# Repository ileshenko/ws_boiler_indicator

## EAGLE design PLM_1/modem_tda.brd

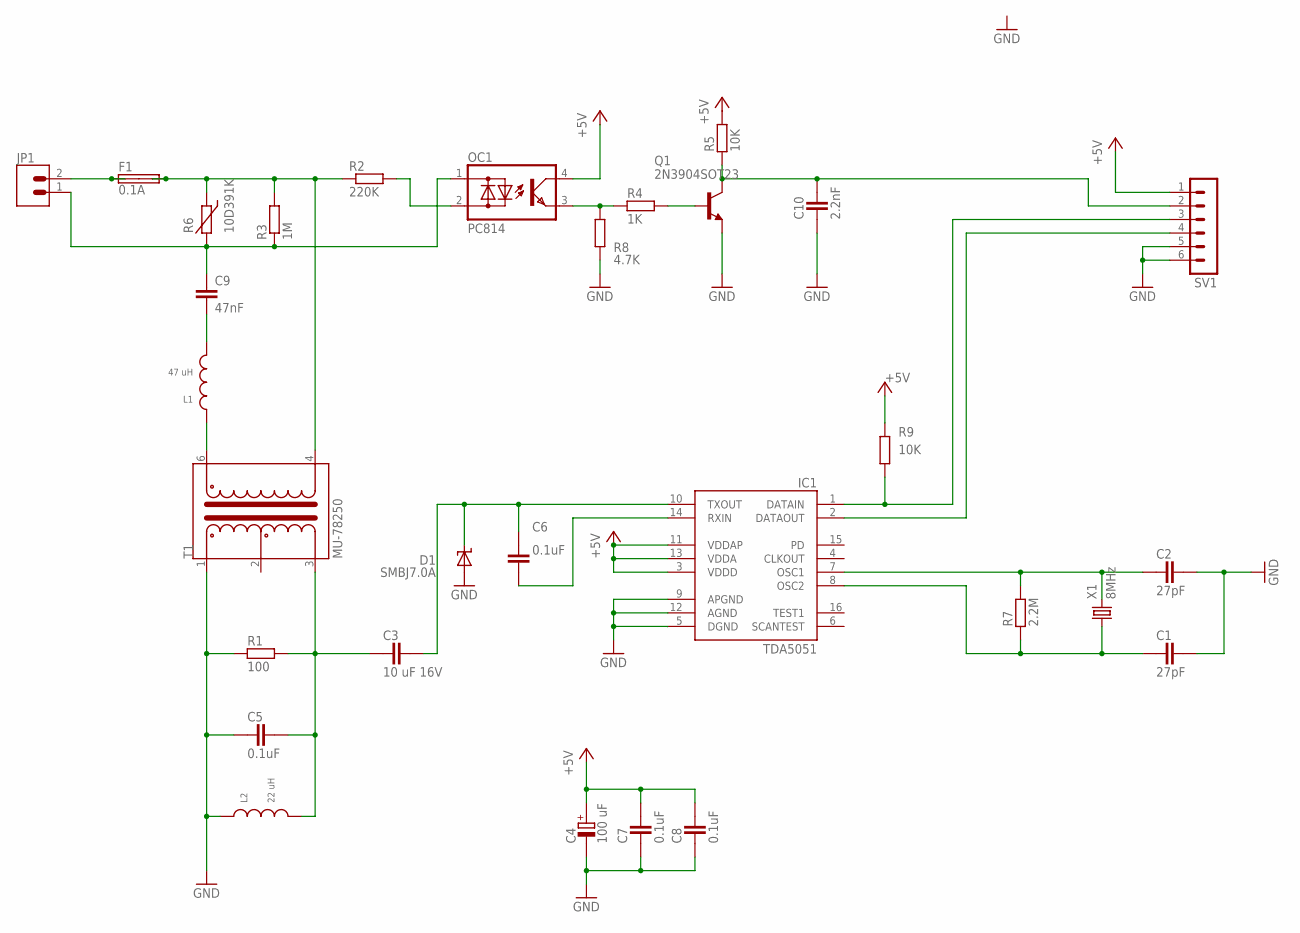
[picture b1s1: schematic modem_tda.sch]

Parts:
C1, C2: 27pF; CAPC2012X145AN
C3: 10 uF 16V; CAPC3215X168N
C4: 100 uF; CAPMP6032X150N
C5, C6, C7, C8: 0.1uF; CAPC2012X145AN
C9: 47nF; XC10B6
C10: 2.2nF; CAPC2012X145AN
D1: SMBJ7.0A; SMBJ
F1: 0.1A; SHK20L
IC1: TDA5051; SO16W
JP1: BLUE_TERM
L1: 47 uH; CD43
L2: 22 uH; CD43
OC1: PC814; DIL04
Q1: 2N3904SOT23; SOT23-BEC
R1: 100; RESC2012X70N
R2: 220K; 0309/12
R3: 1M; 0207/10
R4: 1K; RESC2012X70N
R5, R9: 10K; RESC2012X70N
R6: 10D391K; MOV-10D
R7: 2.2M; RESC2012X70N
R8: 4.7K; RESC2012X70N
SV1: MA06-1
T1: MU-78250; 6-PIN-DIL
X1: 8MHz; HC49/S

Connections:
+5V: C4.+, C7.2, C8.2, IC1.3 (VDDD), IC1.11 (VDDAP), IC1.13 (VDDA), OC1.4 (C), R5.2, R9.2, SV1.1
GND: C1.2, C2.2, C4.-, C5.1, C7.1, C8.1, C10.1, D1.A, IC1.5 (DGND), IC1.9 (APGND), IC1.12 (AGND), L2.1, Q1.E, R1.1, R8.1, SV1.5, SV1.6, T1.1
unnamed: F1.1A, F1.1B, JP1.2
unnamed: F1.2A, F1.2B, R2.1, R3.2, R6.2, T1.4
unnamed: C9.1, JP1.1, OC1.1 (AC1), R3.1, R6.1
unnamed: OC1.2 (AC2), R2.2
unnamed: C9.2, L1.2
unnamed: L1.1, T1.6
unnamed: OC1.3 (E), R4.1, R8.2
unnamed: C3.1, C5.2, L2.2, R1.2, T1.3
unnamed: C3.2, C6.2, D1.C, IC1.10 (TXOUT)
unnamed: C10.2, Q1.C, R5.1, SV1.2
unnamed: C6.1, IC1.14 (RXIN)
unnamed: C2.1, IC1.7 (OSC1), R7.2, X1.2
unnamed: C1.1, IC1.8 (OSC2), R7.1, X1.1
unnamed: IC1.1 (DATAIN), R9.1, SV1.3
unnamed: IC1.2 (DATAOUT), SV1.4
unnamed: Q1.B, R4.2

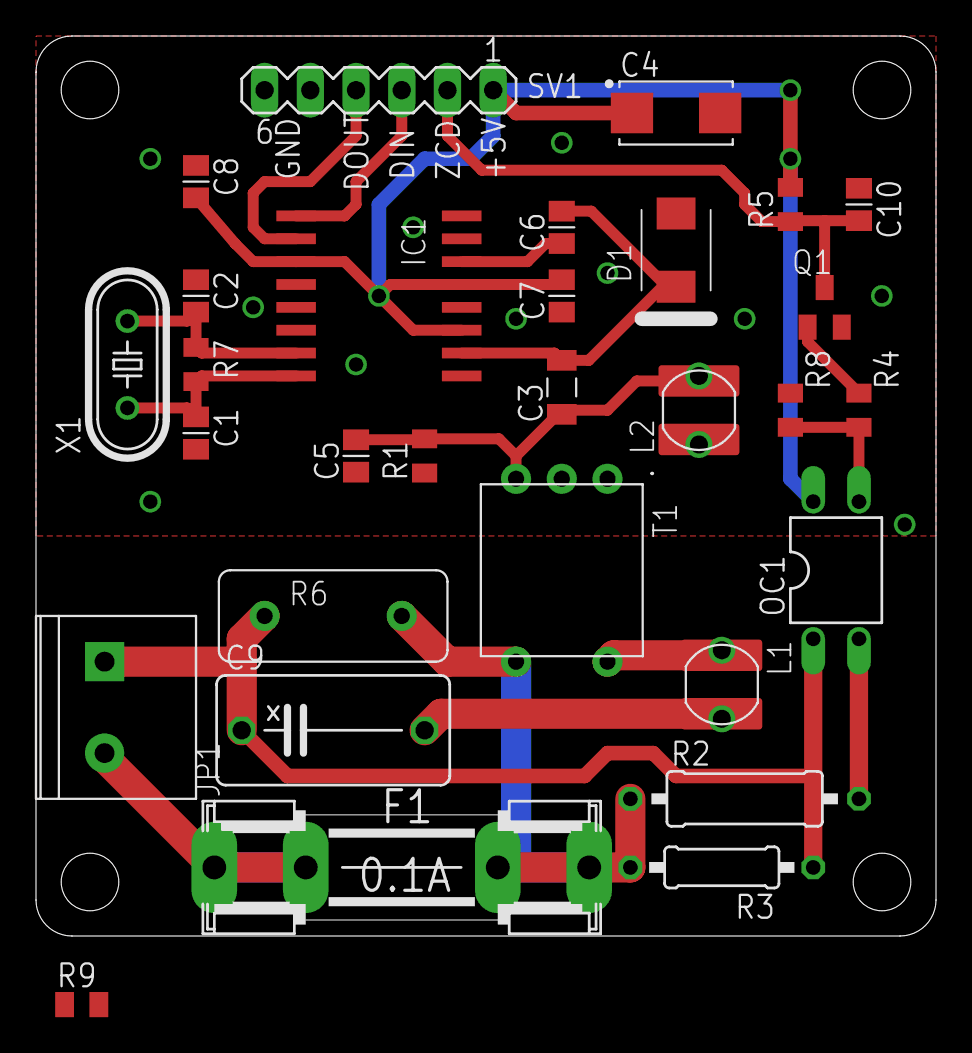
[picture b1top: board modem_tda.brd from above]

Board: 2 copper layers, 50.0 x 50.0 mm, 30 parts (0 on the bottom side), 18 nets.

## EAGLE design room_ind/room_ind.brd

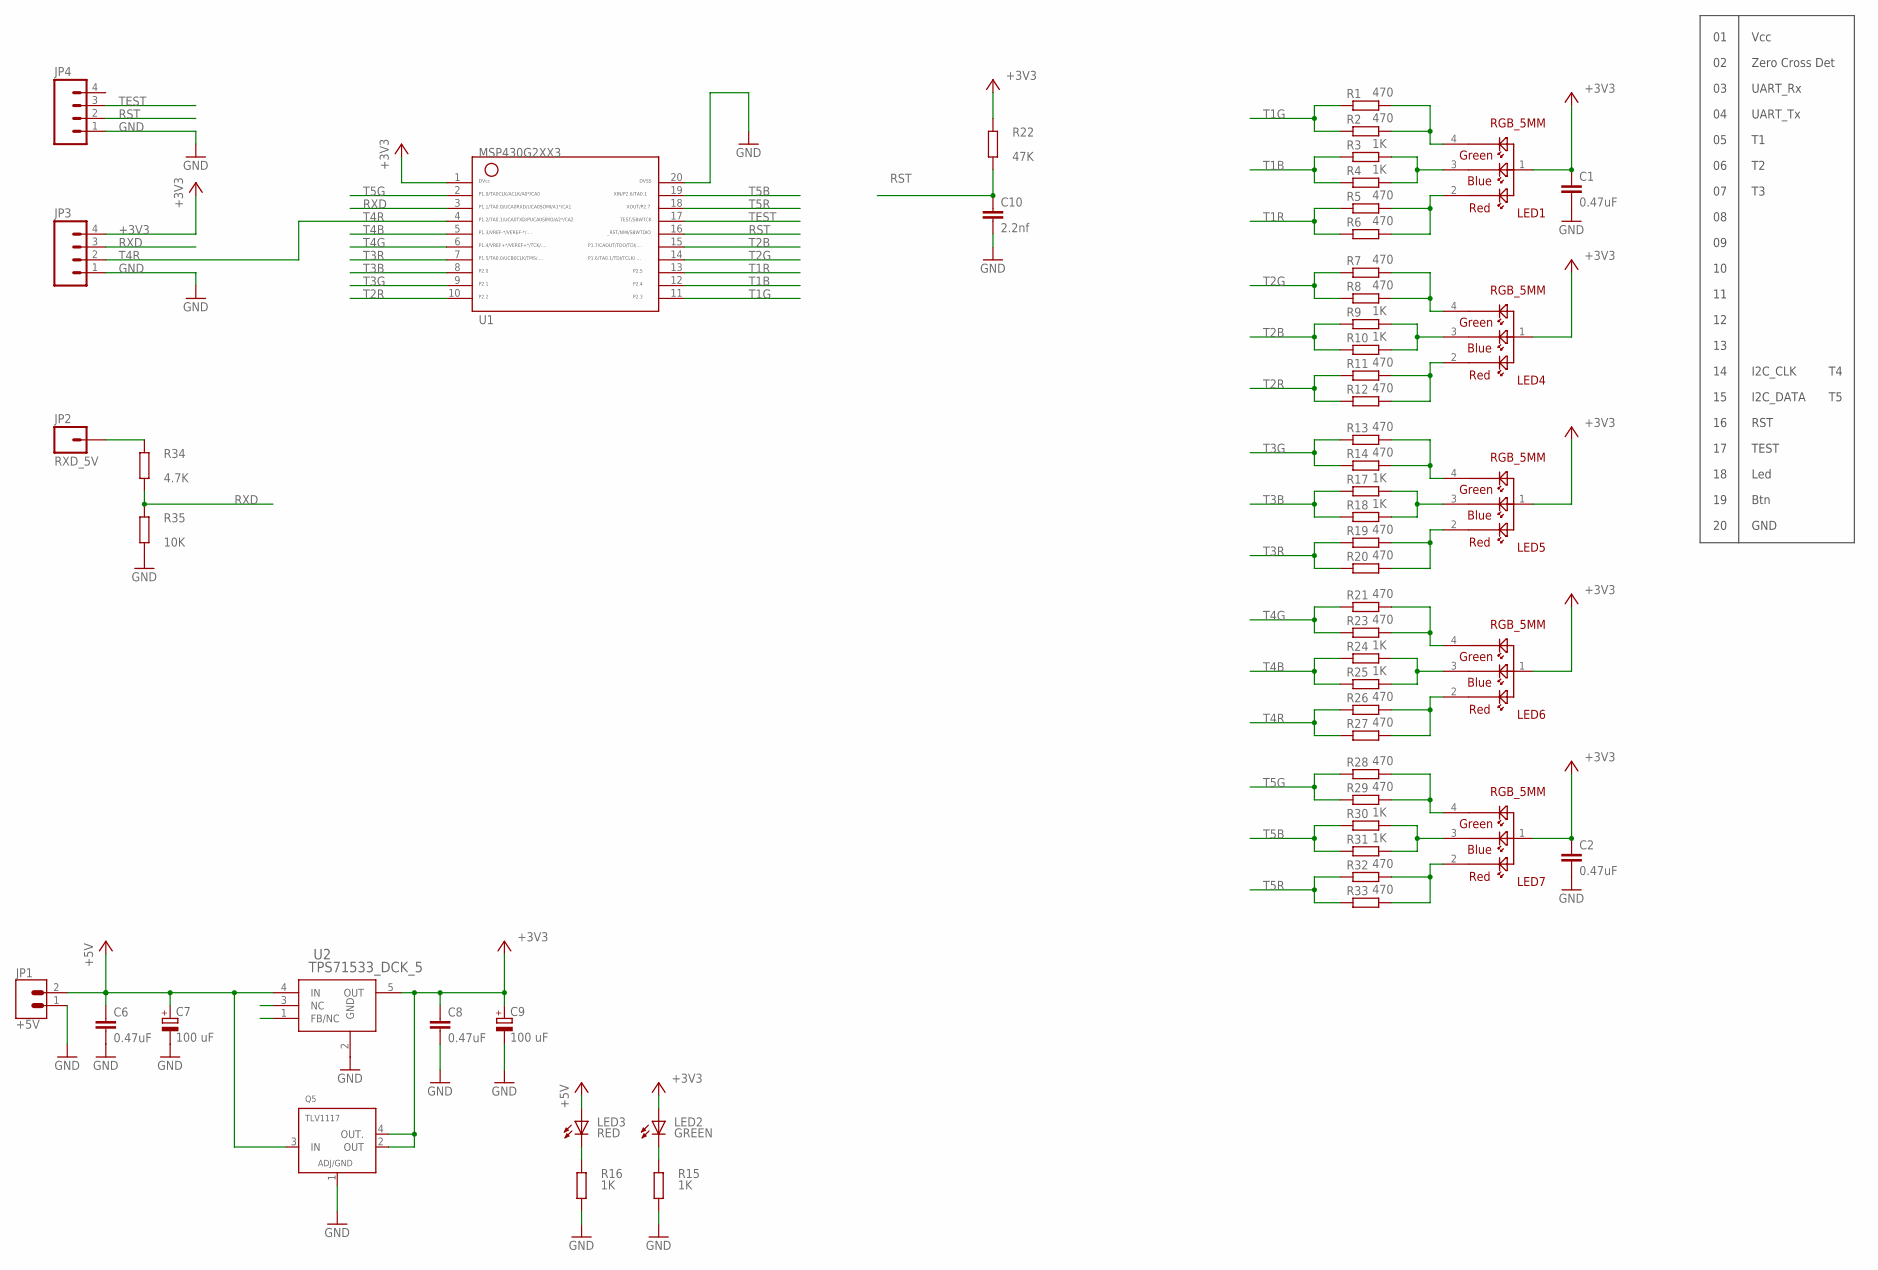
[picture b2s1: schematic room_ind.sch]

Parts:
C1, C2, C6, C8: 0.47uF; C0805
C7, C9: 100 uF; E2,5-7
C10: 2.2nf; C0805
JP1: +5V; BLUE_TERM
JP2: RXD_5V; 1X01
JP3, JP4: M04PTH; 1X04
LED1, LED4, LED5, LED6, LED7: RGB_5MM
LED2: GREEN; CHIP-LED0805
LED3: RED; CHIP-LED0805
Q5: TLV1117; SOT223-4
R1, R5, R7, R11, R13, R19, R21, R26, R28, R32: 470; R0805
R2, R6, R8, R12, R14, R20, R23, R27, R29, R33: 470; 0207/7
R3, R9, R15, R16, R17, R24, R30: 1K; R0805
R4, R10, R18, R25, R31: 1K; 0207/7
R22: 47K; R0805
R34: 4.7K; R0805
R35: 10K; R0805
U1: G2XX3---PW20; PW20
U2: TPS71533_DCK_5; DCK5

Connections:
+3V3: C1.1, C2.1, C8.1, C9.+, JP3.4, LED1.1, LED2.A, LED4.1, LED5.1, LED6.1, LED7.1, Q5.2 (OUT), Q5.4 (OUT.), R22.2, U1.1, U2.5 (OUT)
+5V: C6.1, C7.+, JP1.2, LED3.A, Q5.3 (IN), U2.4 (IN)
GND: C1.2, C2.2, C6.2, C7.-, C8.2, C9.-, C10.2, JP1.1, JP3.1, JP4.1, Q5.1 (ADJ/GND), R15.1, R16.1, R35.1, U1.20, U2.2 (GND)
unnamed: LED1.3, R3.2, R4.2
unnamed: LED1.4, R1.2, R2.2
unnamed: LED1.2, R5.2, R6.2
unnamed: JP2.1, R34.2
unnamed: LED2.C, R15.2
unnamed: LED3.C, R16.2
unnamed: LED4.3, R9.2, R10.2
unnamed: LED4.4, R7.2, R8.2
unnamed: LED4.2, R11.2, R12.2
unnamed: LED5.3, R17.2, R18.2
unnamed: LED5.4, R13.2, R14.2
unnamed: LED5.2, R19.2, R20.2
unnamed: LED6.3, R24.2, R25.2
unnamed: LED6.4, R21.2, R23.2
unnamed: LED6.2, R26.2, R27.2
unnamed: LED7.3, R30.2, R31.2
unnamed: LED7.4, R28.2, R29.2
unnamed: LED7.2, R32.2, R33.2
RST: C10.1, JP4.2, R22.1, U1.16
RXD: JP3.3, R34.1, R35.2, U1.3
T1B: R3.1, R4.1, U1.12
T1G: R1.1, R2.1, U1.11
T1R: R5.1, R6.1, U1.13
T2B: R9.1, R10.1, U1.15
T2G: R7.1, R8.1, U1.14
T2R: R11.1, R12.1, U1.10
T3B: R17.1, R18.1, U1.8
T3G: R13.1, R14.1, U1.9
T3R: R19.1, R20.1, U1.7
T4B: R24.1, R25.1, U1.5
T4G: R21.1, R23.1, U1.6
T4R: JP3.2, R26.1, R27.1, U1.4
T5B: R30.1, R31.1, U1.19
T5G: R28.1, R29.1, U1.2
T5R: R32.1, R33.1, U1.18
TEST: JP4.3, U1.17

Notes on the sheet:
Vcc
GND
UART_Rx
Led
I2C_CLK
I2C_DATA
Btn
UART_Tx
RST
TEST
Zero Cross Det

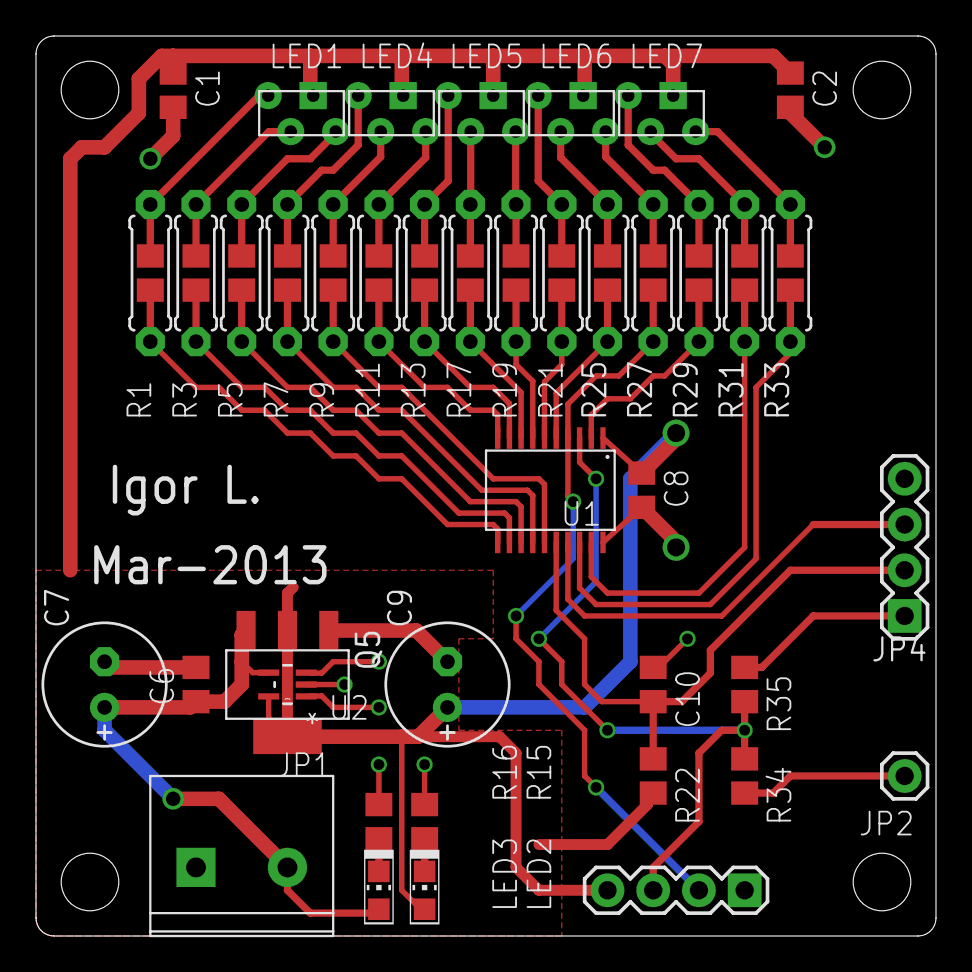
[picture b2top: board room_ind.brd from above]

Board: 2 copper layers, 50.0 x 50.0 mm, 56 parts (0 on the bottom side), 39 nets.

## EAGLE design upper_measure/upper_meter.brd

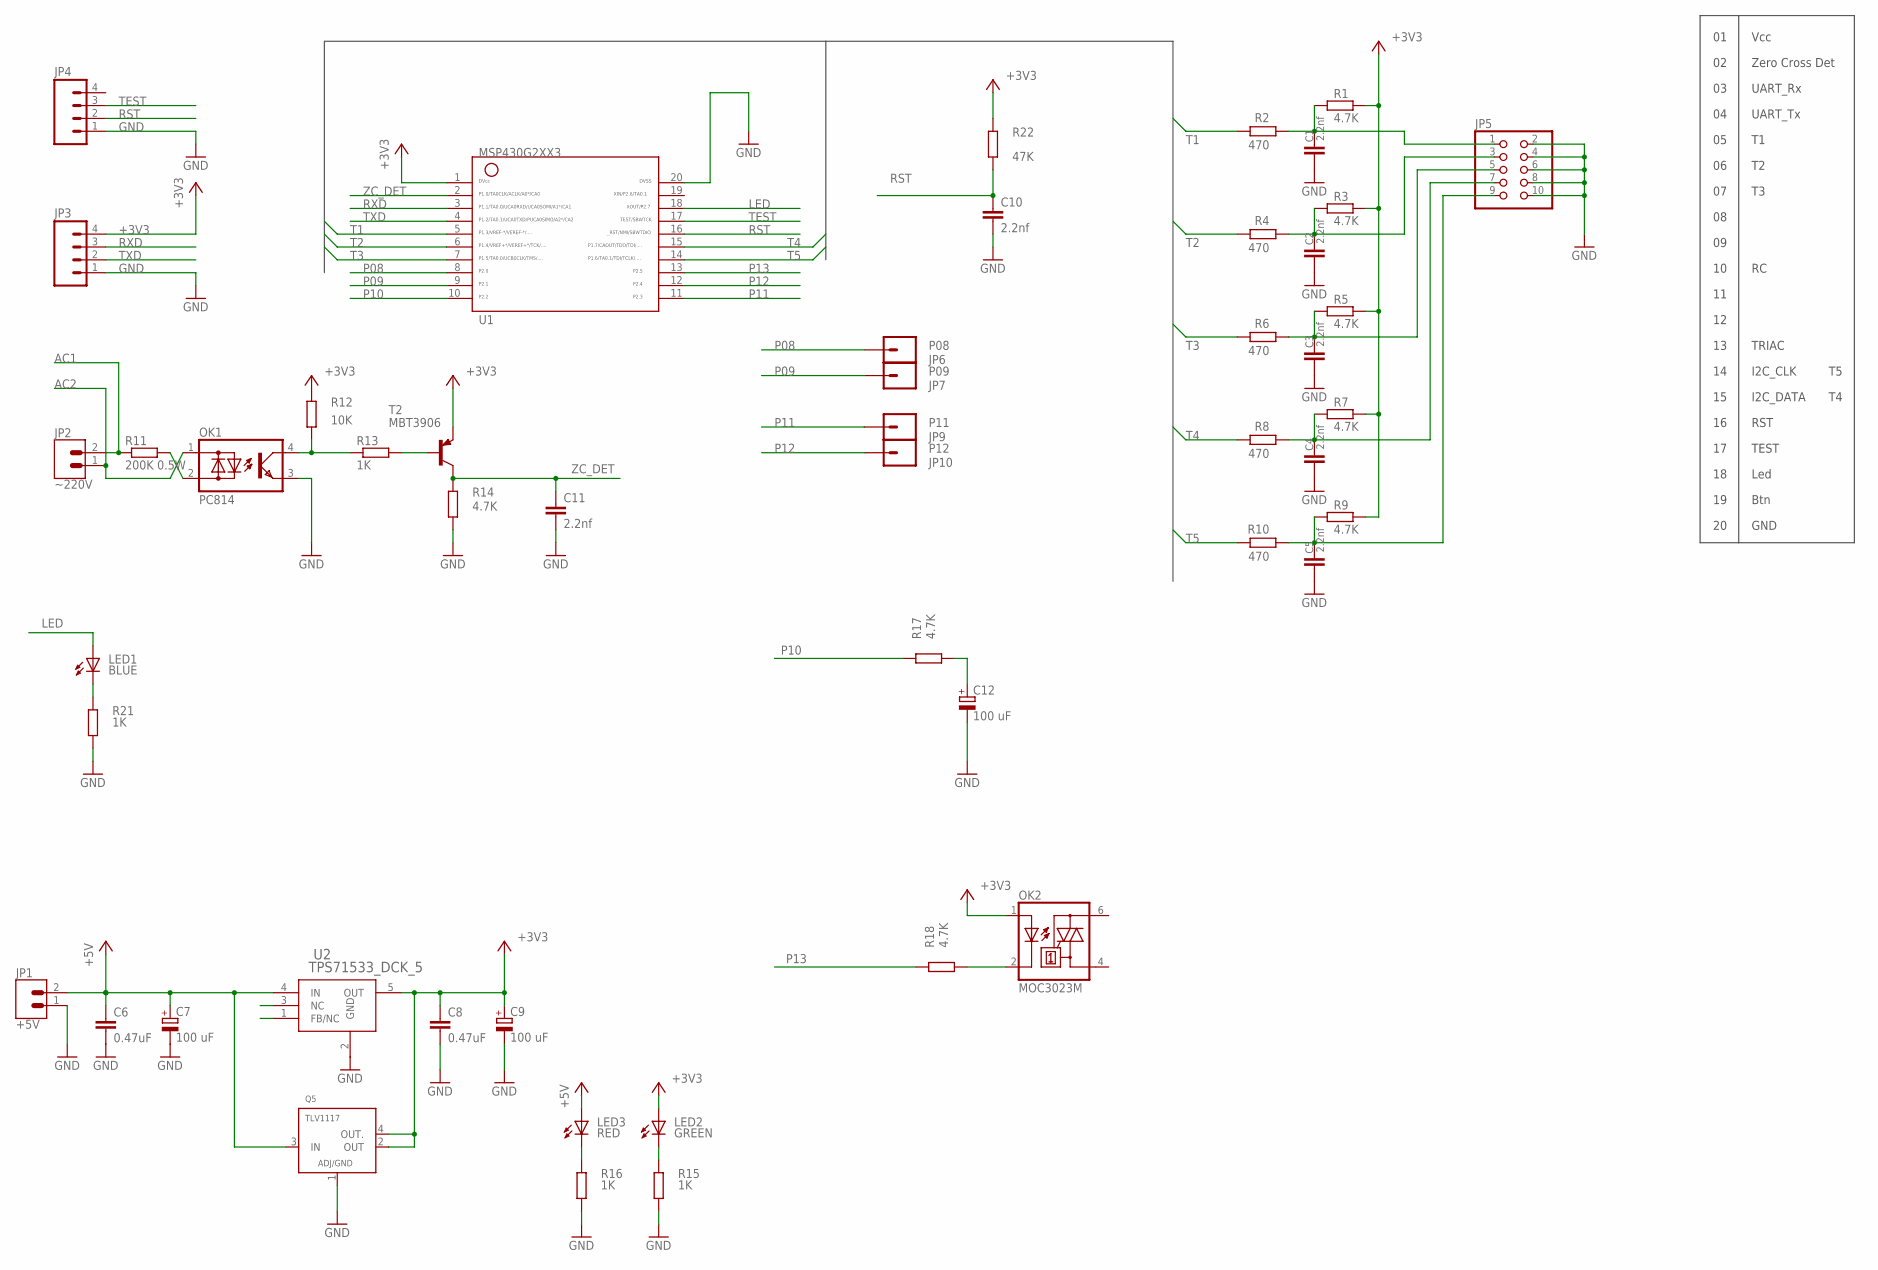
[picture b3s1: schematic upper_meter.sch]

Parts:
C1, C2, C3, C4, C5, C10, C11: 2.2nf; C0805
C6, C8: 0.47uF; C0805
C7, C9, C12: 100 uF; E2,5-7
JP1: +5V; BLUE_TERM
JP2: ~220V; BLUE_TERM
JP3, JP4: M04PTH; 1X04
JP5: PINHD-2X5; 2X05
JP6: P08; 1X01
JP7: P09; 1X01
JP9: P11; 1X01
JP10: P12; 1X01
LED1: BLUE; CHIP-LED0805
LED2: GREEN; CHIP-LED0805
LED3: RED; CHIP-LED0805
OK1: PC814; DIL04
OK2: MOC3023M; DIL06
Q5: TLV1117; SOT223-4
R1, R3, R5, R7, R9, R14, R17, R18: 4.7K; R0805
R2, R4, R6, R8, R10: 470; R0805
R11: 200K 0.5W; 0309/12
R12: 10K; R0805
R13, R15, R16, R21: 1K; R0805
R22: 47K; R0805
T2: MBT3906; SOT23-BEC
U1: G2XX3---PW20; PW20
U2: TPS71533_DCK_5; DCK5

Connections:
+3V3: C8.1, C9.+, JP3.4, LED2.A, OK2.1 (A), Q5.2 (OUT), Q5.4 (OUT.), R1.1, R3.1, R5.1, R7.1, R9.1, R12.2, R22.2, T2.E, U1.1, U2.5 (OUT)
+5V: C6.1, C7.+, JP1.2, LED3.A, Q5.3 (IN), U2.4 (IN)
AC1: JP2.2, R11.1
AC2: JP2.1, OK1.1 (AC1)
GND: C1.1, C2.1, C3.1, C4.1, C5.1, C6.2, C7.-, C8.2, C9.-, C10.2, C11.2, C12.-, JP1.1, JP3.1, JP4.1, JP5.2, JP5.4, JP5.6, JP5.8, JP5.10, OK1.3 (E), Q5.1 (ADJ/GND), R14.1, R15.1, R16.1, R21.1, U1.20, U2.2 (GND)
LED: LED1.A, U1.18
unnamed: C2.2, JP5.3, R3.2, R4.2
unnamed: C1.2, JP5.1, R1.2, R2.2
unnamed: C3.2, JP5.5, R5.2, R6.2
unnamed: C4.2, JP5.7, R7.2, R8.2
unnamed: C5.2, JP5.9, R9.2, R10.2
unnamed: R13.2, T2.B
unnamed: LED2.C, R15.2
unnamed: LED3.C, R16.2
unnamed: OK1.4 (C), R12.1, R13.1
unnamed: C12.+, R17.1
unnamed: OK2.2 (C), R18.1
unnamed: OK1.2 (AC2), R11.2
unnamed: LED1.C, R21.2
P08: JP6.1, U1.8
P09: JP7.1, U1.9
P10: R17.2, U1.10
P11: JP9.1, U1.11
P12: JP10.1, U1.12
P13: R18.2, U1.13
RST: C10.1, JP4.2, R22.1, U1.16
RXD: JP3.3, U1.3
T1: R2.1, U1.5
T2: R4.1, U1.6
T3: R6.1, U1.7
T4: R8.1, U1.15
T5: R10.1, U1.14
TEST: JP4.3, U1.17
TXD: JP3.2, U1.4
ZC_DET: C11.1, R14.2, T2.C, U1.2

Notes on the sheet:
Vcc
GND
UART_Rx
Led
I2C_CLK
I2C_DATA
Btn
UART_Tx
RST
TEST
Zero Cross Det
TRIAC

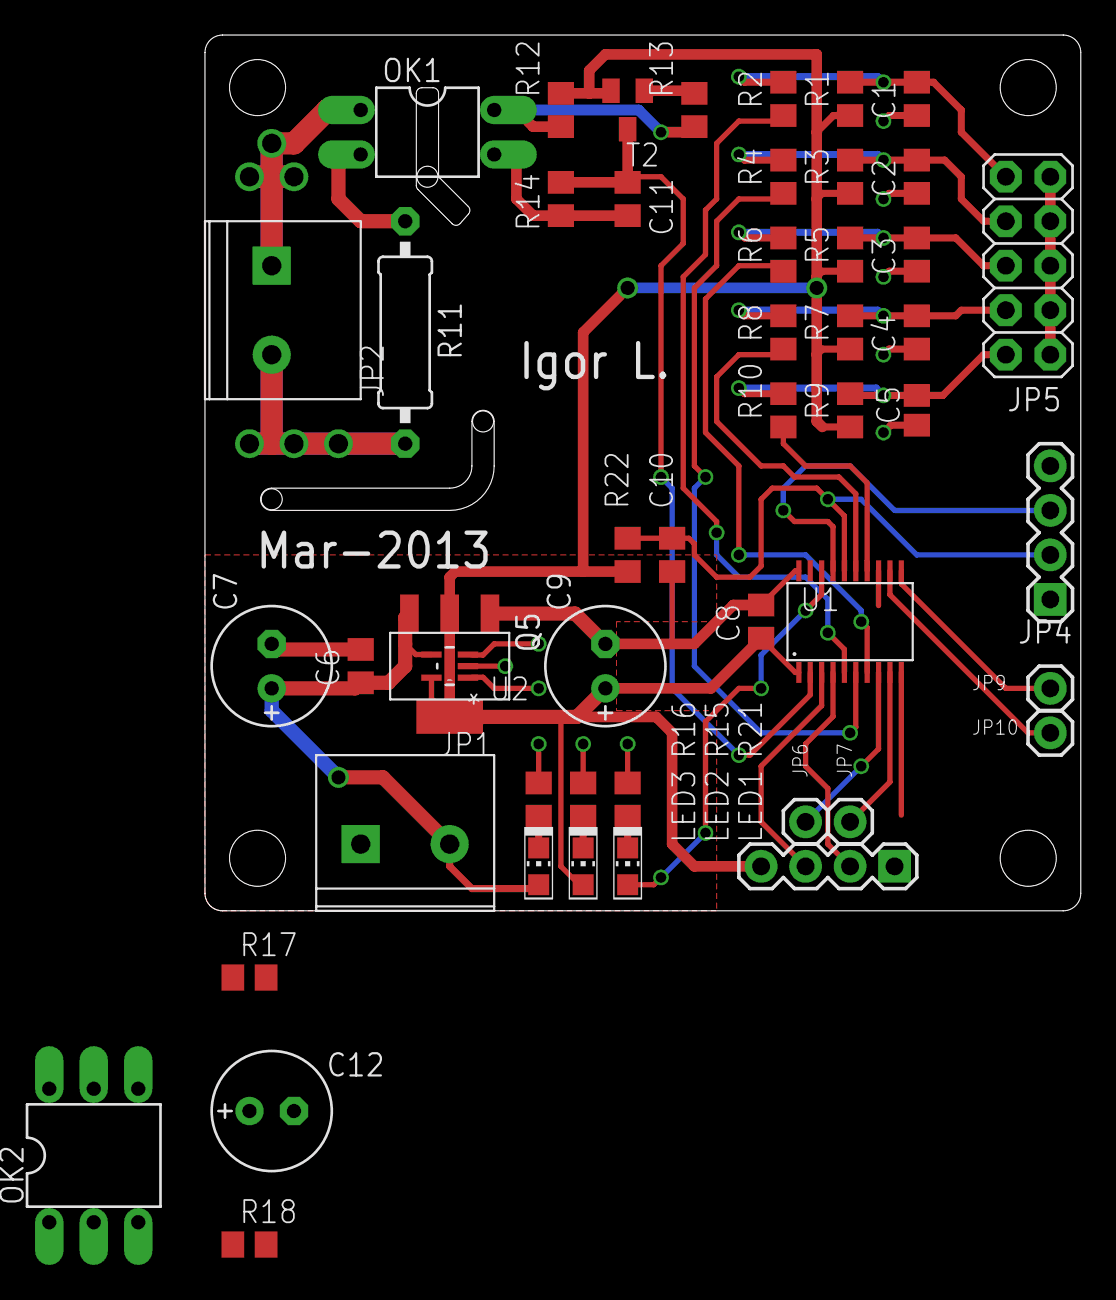
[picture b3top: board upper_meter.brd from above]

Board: 2 copper layers, 50.0 x 50.0 mm, 50 parts (0 on the bottom side), 35 nets.

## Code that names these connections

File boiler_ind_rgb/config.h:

/* Global config file */
#ifndef _CONFIG_H_
#define _CONFIH_H_

/* Timer section */
//#define USE_ALARM


/* UART section */
#define UART_BAUDRATE 300

//#define REPORT_SZ

/* LEDS section */
//#define LEDP 2

//#define LEDB BIT7
//#define OUT1B BIT2
//#define OUT2B BIT3
//#define LEDS (LEDB /*| OUT1B | OUT2B*/)

#if 0
/* Buttons section */
#define BTNP 2

#define CNT1B BIT0
#define CNT2B BIT1
#define BTNB BIT6
#define BTN220B BIT5

#define BTNS (CNT1B | CNT2B | BTNB | BTN220B)
*/
#endif

#if 0
/* Temperature section */
#define T_CNT 5
#define MAXTEMP 140

#define T1B BIT3
#define T1P 3
#define T2B BIT4
#define T2P 4
#define T3B BIT5
#define T3P 5
#define T4B BIT7
#define T4P 7
#define T5B BIT6
#define T5P 6
#define TS (T1B | T2B | T3B | T4B | T5B)

#define T1T ntc1033470
#define T2T ntc1033470
#define T3T ntc1033470
#define T4T ntc1033470
#define T5T ntc1033470
#endif
//#define T_UP 0
//#define T_DOWN 1

#endif

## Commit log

2013-04-15 initial version
2013-04-27 inbox first demo
2013-11-22 shorten Hello blinking
2013-11-22 add workspace under GIT
2013-11-26 ignore unimportant files from metadata
2013-11-26 generic project changes
2013-11-26 disable unimportant info (ULP) messages
2013-12-17 x10 works in demo mode. Bedore cleaning.
2014-01-10 One percent of code clearance.
2014-01-27 Version with relay. Works on roof for me and EyalB
2014-01-27 sync msp430_lib with etalone
2014-02-19 Fix bug "default state is not shown, if all sensors under 25 degrees"
2014-02-19 After switch on - only indication, not heating.
2014-07-14 move project from common eagle repository under comon with firmware repo
2014-07-21 add first production files

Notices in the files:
parts and their libraries:
SparkFun: Licensing: CC v3.0 Share-Alike You are welcome to use this library for commercial purposes.
